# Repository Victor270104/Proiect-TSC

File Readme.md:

# OpenBook

**Autor:** Sandu Victor, 332CC

---

## 1. Descriere generală

Acest proiect propune o platformă hardware pentru dezvoltarea de aplicații IoT și afișare e-paper, cu consum redus de energie. Elementul central este microcontrollerul **ESP32-C6-WROOM-1**, care oferă conectivitate Wi-Fi 6 și Bluetooth Low Energy. Sistemul este proiectat pentru a funcționa atât conectat la USB-C, cât și alimentat de la o baterie Li-Po.

---

## 2. Caracteristici cheie

- **Alimentare prin USB-C**: Simplifică programarea și încărcarea bateriei.
- **Microcontroller ESP32-C6**: Include nucleu RISC-V, Wi-Fi 6, BLE și memorie flash internă de 8MB.
- **Senzori integrați**: BME688 (temperatură, umiditate, presiune, gaze) și DS3231 (ceas de timp real).
- **Stocare suplimentară**:
  - Card SD (SPI)
  - Memorie NOR Flash (W25Q512)
- **Afișaj E-Paper**: Consum ultra-redus, actualizare doar la nevoie.
- **Monitorizare baterie**: MAX17048 pentru nivelul de încărcare.

---

## 3. Structură hardware (sumar)

- **USB-C** și protecții ESD (varistori, diodă TVS).
- **Circuit încărcare Li-Po** cu MCP73831.
- **Regulator LDO** pentru 3.3V stabil.
- **Microcontrollerul ESP32-C6-WROOM-1** (SPI, I2C, GPIO).
- **Senzori**:
  - BME688 (I2C)
  - DS3231 (I2C)
- **Memorii**:
  - Card SD (SPI)
  - W25Q512 (SPI)
- **E-Paper** cu driver SPI și alimentare comutabilă (MOSFET).
- **Butoane** de RESET și BOOT.

*(Diagrama de mai sus este inclusă din `Images/Diagrama.png`.)*

---

## 4. Bill of Materials (BOM)

| Component  | Supplier Link | Datasheet |
|------------|---------------|-----------|
| 112A-TAAR-R03 | [Model](https://store.comet.srl.ro/Catalogue/Product/43497/) | [Datasheet](https://www.snapeda.com/parts/112A-TAAR-R03/Attend/datasheet/) |
| 744043680 | [Model](https://ro.mouser.com/ProductDetail/Wurth-Elektronik/744043680?qs=PGXP4M47uW6VkZq%252BkzjrHA%3D%3D) | [Datasheet](https://www.we-online.com/components/products/datasheet/744043680.pdf) |
| BD5229G-TR | [Model](https://componentsearchengine.com/part-view/BD5229G-TR/ROHM%20Semiconductor) | [Datasheet](https://fscdn.rohm.com/en/products/databook/datasheet/ic/power/voltage_detector/bd52xxg-e.pdf) |
| Capacitor 0402 | [Model](https://ro.mouser.com/c/passive-components/capacitors/ceramic-capacitors/?q=CC0402&srsltid=AfmBOoogjqwwed3xvp6V5-bfVkRuawirfMcnAC47L-UQdC3mnXJk097M) | [Datasheet](https://componentsearchengine.com/Datasheets/2/CC0402MRX5R5BB106.pdf) |
| CPH3225A | [Model](https://www.snapeda.com/parts/CPH3225A/Seiko+Instruments/view-part/?ref=snap) | [Datasheet](https://www.snapeda.com/parts/CPH3225A/Seiko%20Instruments/datasheet/) |
| Custom Button | [Model](https://industry.panasonic.com/global/en/products/control/switch/light-touch/number/evqpuj02k) | [Datasheet](https://industry.panasonic.com/global/en/downloads?tab=catalog&small_g_cd=203&part_no=EVQPUJ02K) |
| DS3231SN | [Model](https://www.snapeda.com/parts/DS3231SN%23/Analog+Devices/view-part/?ref=eda) | [Datasheet](https://www.snapeda.com/parts/DS3231SN%23/Analog%20Devices/datasheet/) |
| ESP32 WROVER 0805 Capacitor | [Model]() | [Datasheet]() |
| ESP32 WROVER BME680 Sensor | [Model](https://www.snapeda.com/parts/BME680/Bosch/view-part/?welcome=home) | [Datasheet](https://www.bosch-sensortec.com/media/boschsensortec/downloads/datasheets/bst-bme680-ds001.pdf) |
| ESP32 WROVER MCP73831 Power Management | [Model](https://www.snapeda.com/parts/BME680/Bosch/view-part/?welcome=home) | [Datasheet](https://www.snapeda.com/parts/MCP73831T-2ACI/OT/Microchip/datasheet/) |
| ESP32C6 Varistor 1812 | [Model]() | [Datasheet]() |
| ESP32C6 WROOM-1-N8| [Model](https://www.snapeda.com/parts/ESP32-C6-WROOM-1-N8/Espressif+Systems/view-part/?ref=eda) | [Datasheet](https://www.snapeda.com/parts/ESP32-C6-WROOM-1-N8/Espressif%20Systems/datasheet/) |
| FH34SRJ-24S-0.5SH | [Model](https://ro.mouser.com/ProductDetail/Hirose-Connector/FH34SRJ-24S-0.5SH99?qs=vcbW%252B4%252BSTIpKBl5ap9J8Fw%3D%3D) | [Datasheet](https://www.snapeda.com/parts/FH34SRJ-24S-0.5SH(99)/Hirose%20Connector/datasheet/) |
| LED Chip 0603 | [Model](https://www.snapeda.com/parts/KP-1608SURCK/Kingbright/view-part/?ref=search&t=LED%200603) | [Datasheet](https://www.snapeda.com/parts/KP-1608SURCK/Kingbright/datasheet/) |
| MAX17048G+T10 | [Model](https://www.snapeda.com/parts/MAX17048G+T10/Analog+Devices/view-part/?ref=eda) | [Datasheet](https://www.snapeda.com/parts/MAX17048G+T10/Analog%20Devices/datasheet/) |
| MBR0530 Schottky Diode | [Model](https://www.snapeda.com/parts/MBR0530/Onsemi/view-part/?ref=snap) | [Datasheet](https://www.snapeda.com/parts/MBR0530/ON%20Semiconductor/datasheet/) |
| PGB1010603MR | [Model](https://www.snapeda.com/parts/PGB1010603MR/Littelfuse/view-part/?ref=eda) | [Datasheet](https://www.snapeda.com/parts/PGB1010603MR/Littelfuse%20Inc./datasheet/) |
| QWIIC Connector | [Model](https://www.snapeda.com/parts/PRT-14417/SparkFun/view-part/) | [Datasheet](https://www.snapeda.com/parts/PRT-14417/SparkFun%20Electronics/datasheet/) |
| RCL CPOL 3528 | [Model](https://www.snapeda.com/parts/CPH3225A/Seiko+Instruments/view-part/?ref=eda) | [Datasheet](https://s3.amazonaws.com/snapeda/datasheet/TAJB475K025RNJ_AVX.pdf) |
| Resistor 0402 | [Model](https://grabcad.com/library/resistor-0402-1) | [Datasheet](https://www.yageo.com/upload/media/product/products/datasheet/rchip/PYu-RC_Group_51_RoHS_L_12.pdf) |
| SI1308EDL-T1-GE3 MOSFET | [Model](https://www.snapeda.com/parts/SI1308EDL-T1-GE3/Vishay+Siliconix/view-part/?welcome=home&ref=eda) | [Datasheet](https://www.snapeda.com/parts/SI1308EDL-T1-GE3/Vishay%20Siliconix/datasheet/) |
| SJ | [Model](https://grabcad.com/library/solder-jumpers-1) | [Datasheet]() |
| USB4110-GF-A | [Model](https://componentsearchengine.com/part-view/USB4110-GF-A/GCT%20(GLOBAL%20CONNECTOR%20TECHNOLOGY)) | [Datasheet](https://gct.co/files/drawings/usb4110.pdf) |
| USBLC6-2SC6Y | [Model](https://www.snapeda.com/parts/USBLC6-2SC6Y/STMicroelectronics/view-part/?welcome=home&ref=eda) | [Datasheet](https://www.snapeda.com/parts/USBLC6-2SC6Y/STMicroelectronics/datasheet/) |
| W25Q512JVEIQ | [Model](https://www.snapeda.com/parts/W25Q512JVEIQ/Winbond+Electronics/view-part/?ref=eda) | [Datasheet](https://www.winbond.com/resource-files/W25Q512JV%20SPI%20RevB%2006252019%20KMS.pdf) |
| XC6220A331MR-G | [Model](https://componentsearchengine.com/part-view/XC6220A331MR-G/Torex) | [Datasheet](https://product.torexsemi.com/system/files/series/xc6220.pdf) |

## 5. Mapare pini ESP32-C6

| Component                | ESP32-C6 Pin(s) | Interface | Purpose |
|--------------------------|----------------|-----------|---------|
| **E-Paper Display**      | IO7 (MOSI), IO6 (SCK), IO10 (CS), IO5 (DC), IO23 (RST), IO3 (BUSY) | SPI | Transfers image data to the display and controls its state. |
| **MicroSD Card**         | IO7 (MOSI), IO6 (SCK), IO4 (SS_SD), IO2 (MISO) | SPI | Allows storage and retrieval of e-book files. |
| **Environmental Sensor (BME688)** | IO21 (SDA), IO22 (SCL) | I2C | Reads temperature, humidity, pressure, and air quality data. |
| **RTC Module (DS3231)**  | IO21 (SDA), IO22 (SCL), IO18 (RST), IO1 (32KHz), IO0 (INT_RTC) | I2C | Keeps track of time even when ESP32 is off. |
| **External NOR Flash**   | IO11 (CS), IO6 (SCK), IO2 (MISO), IO7 (MOSI) | SPI | Provides additional storage for application data. |
| **Battery Monitoring**   | IO21 (SDA), IO22 (SCL) | I2C | Reads battery voltage and charge status. |
| **USB-C Connection**     | GPIOs through voltage regulation | USB | Powers and programs the ESP32-C6. |
| **Control Buttons**      | IO9 (BOOT), IO15 (CHANGE), EN (RESET) | GPIO | User input for device interactions. |
|

## 6. Consum de energie (exemplu)

| Component                | Current Draw (mA) | Voltage (V) | Power (mW) |
|--------------------------|------------------|-------------|------------|
| ESP32-C6 (Wi-Fi active)  |200               |3.3          |660
| E-Paper Display (Updating)               | 40               | 3.3         | 132        |
| BME688 Sensor (Measuring)| 3.1              | 3.3         | 10.23      |
| RTC Module (Active)      | 0.15             | 3.3         | 0.495      |
| SD Card (Active)         | 50               | 3.3         | 165        |
| Externar NOR Flash       | 25               | 3.3         | 82.5       |
| Total Estimated Power Consumption               | ~318.5mA         | 3.3         | 1050.72    |

## 7. Descriere functionala hardware 

###  Arhitectura Hardware

Sistemul este bazat pe microcontrollerul **ESP32-C6-WROOM-1**, cu conectivitate Wi-Fi 6 și BLE, gândit pentru funcționare autonomă și consum redus de energie. Dispozitivul este alimentat de la o baterie Li-Po și poate fi programat prin USB-C. Componentele sunt interconectate prin SPI, I2C și GPIO.

---

### Alimentare și management baterie

- **USB-C Connector & ESD Protection**  
  Conector: `USB4110-GF-A`  
  Protecție ESD: `USBLC6-2SC6Y`

- **LDO Voltage Regulator**  
  Asigură 3.3V stabil pentru întreaga placă

- **Li-Po Battery Charger**  
  MCP73831 – circuit dedicat pentru încărcarea bateriei

- **Battery Gauge (MAX17048)**  
  Măsoară nivelul bateriei și comunică prin I2C

---

### Microcontroller principal

- **ESP32-C6-WROOM-1-N8**  
  RISC-V MCU cu Wi-Fi 6, BLE, 8MB flash intern  
  Rol: control central, comunicare cu senzori, logare, afișare

---

### Stocare

- **SD Card** – pentru loguri de date, firmware, fișiere
- **W25Q512 NOR Flash** – pentru memorie suplimentară SPI (64Mbit)

---

### Senzori & Ceas

- **BME688** – măsoară temperatură, umiditate, presiune și gaze (I2C)
- **DS3231** – ceas de timp real, cu precizie ridicată (I2C)

---

### Afișaj

- **E-Paper Driver + Conector**  
  Conectat prin SPI, controlat de ESP32  
  Alimentarea este comutabilă cu un MOSFET (SI1308EDL)

---

### Control și testare

- **Reset / Boot Buttons**
- **Qwiic/Stemma QT Connector** – extensii I2C
- **Test Pads** – debugging ușor

---

### Protecții

- **TVS Diodes**: `PGB1010603MR` – protecție ESD pe linii sensibile
- **Varistori**: protecție la supratensiuni

---

## 9. Note Adiționale de Proiectare

### Ajustări ale Footprint-urilor

- **Diode (SMD-Hole)**: Footprint-ul inițial avea orificiile pad-urilor prea mici, ceea ce ar fi putut cauza probleme la lipire. Dimensiunea pad-urilor a fost actualizată la **35mil x 190mil** pentru a asigura o producibilitate bună și o conexiune electrică fiabilă.

- **U4 – MAX17048G+T10**: Calea de alimentare VBAT a fost proiectată cu o lățime de **0,3 mm**, pe baza constrângerilor de implementare. Totuși, în footprint, pinii aveau numai **0,27 mm**, cauzând asimetrie și rutare inconsistentă. Dimensiunile pinilor au fost ajustate pentru a se potrivi cu lățimea traseului și a menține simetria designului.

---

### Rutare & Plan de Masă

- **Traseele de alimentare** au fost rutate exclusiv pe stratul superior (Top Layer), necesitând aproximativ **150 de via-uri** pentru a permite rutarea semnalelor pe stratul inferior (Bottom Layer).
- **Planul de masă (GND)** a fost adăugat după ce rutarea a fost finalizată, aplicându-se atât pe stratul superior, cât și pe cel inferior, pentru a obține o împământare cu impedanță redusă și pentru a diminua interferențele EMI.

---

### Poziționarea Componentelor

- **Porturile externe** au fost aliniate cu atenție în raport cu carcasa personalizată OpenBook, pentru a asigura o potrivire corectă și acces ușor.
- **Pad-urile de test (TP)** au fost plasate în apropierea marginilor plăcii și în zone accesibile, pentru a facilita depanarea și testarea.
- **Condenzatoarele de decuplare 100nF** au fost poziționate cât mai aproape de pinii de alimentare ai circuitelor integrate, în conformitate cu practicile standard de reducere a zgomotului.

---

### Probleme de Schematice & Modele 3D

- **Net „GND1”**: A apărut în schematică un net denumit „GND1”, însă acesta nu era vizibil și nu era funcțional conectat la masă. Se presupune că a fost un artefact apărut în timpul procesului de proiectare.
- **Ordinea pinilor la componente 3D**: După finalizarea rutării, actualizarea modelelor 3D a inversat ordinea pinilor la anumite componente cu 2 pini, rupând conexiunile existente. S-a rezolvat prin rotirea acelor modele cu **180°** și realinierea pinilor.

---

### Carcasă & Integrare 3D

- A fost creată o versiune alternativă a carcasei OpenBook, care include o **culoare personalizată** pentru un aspect unic.
- Componentele 3D au fost importate în două moduri diferite, în funcție de frecvența cu care apăreau în schematică.

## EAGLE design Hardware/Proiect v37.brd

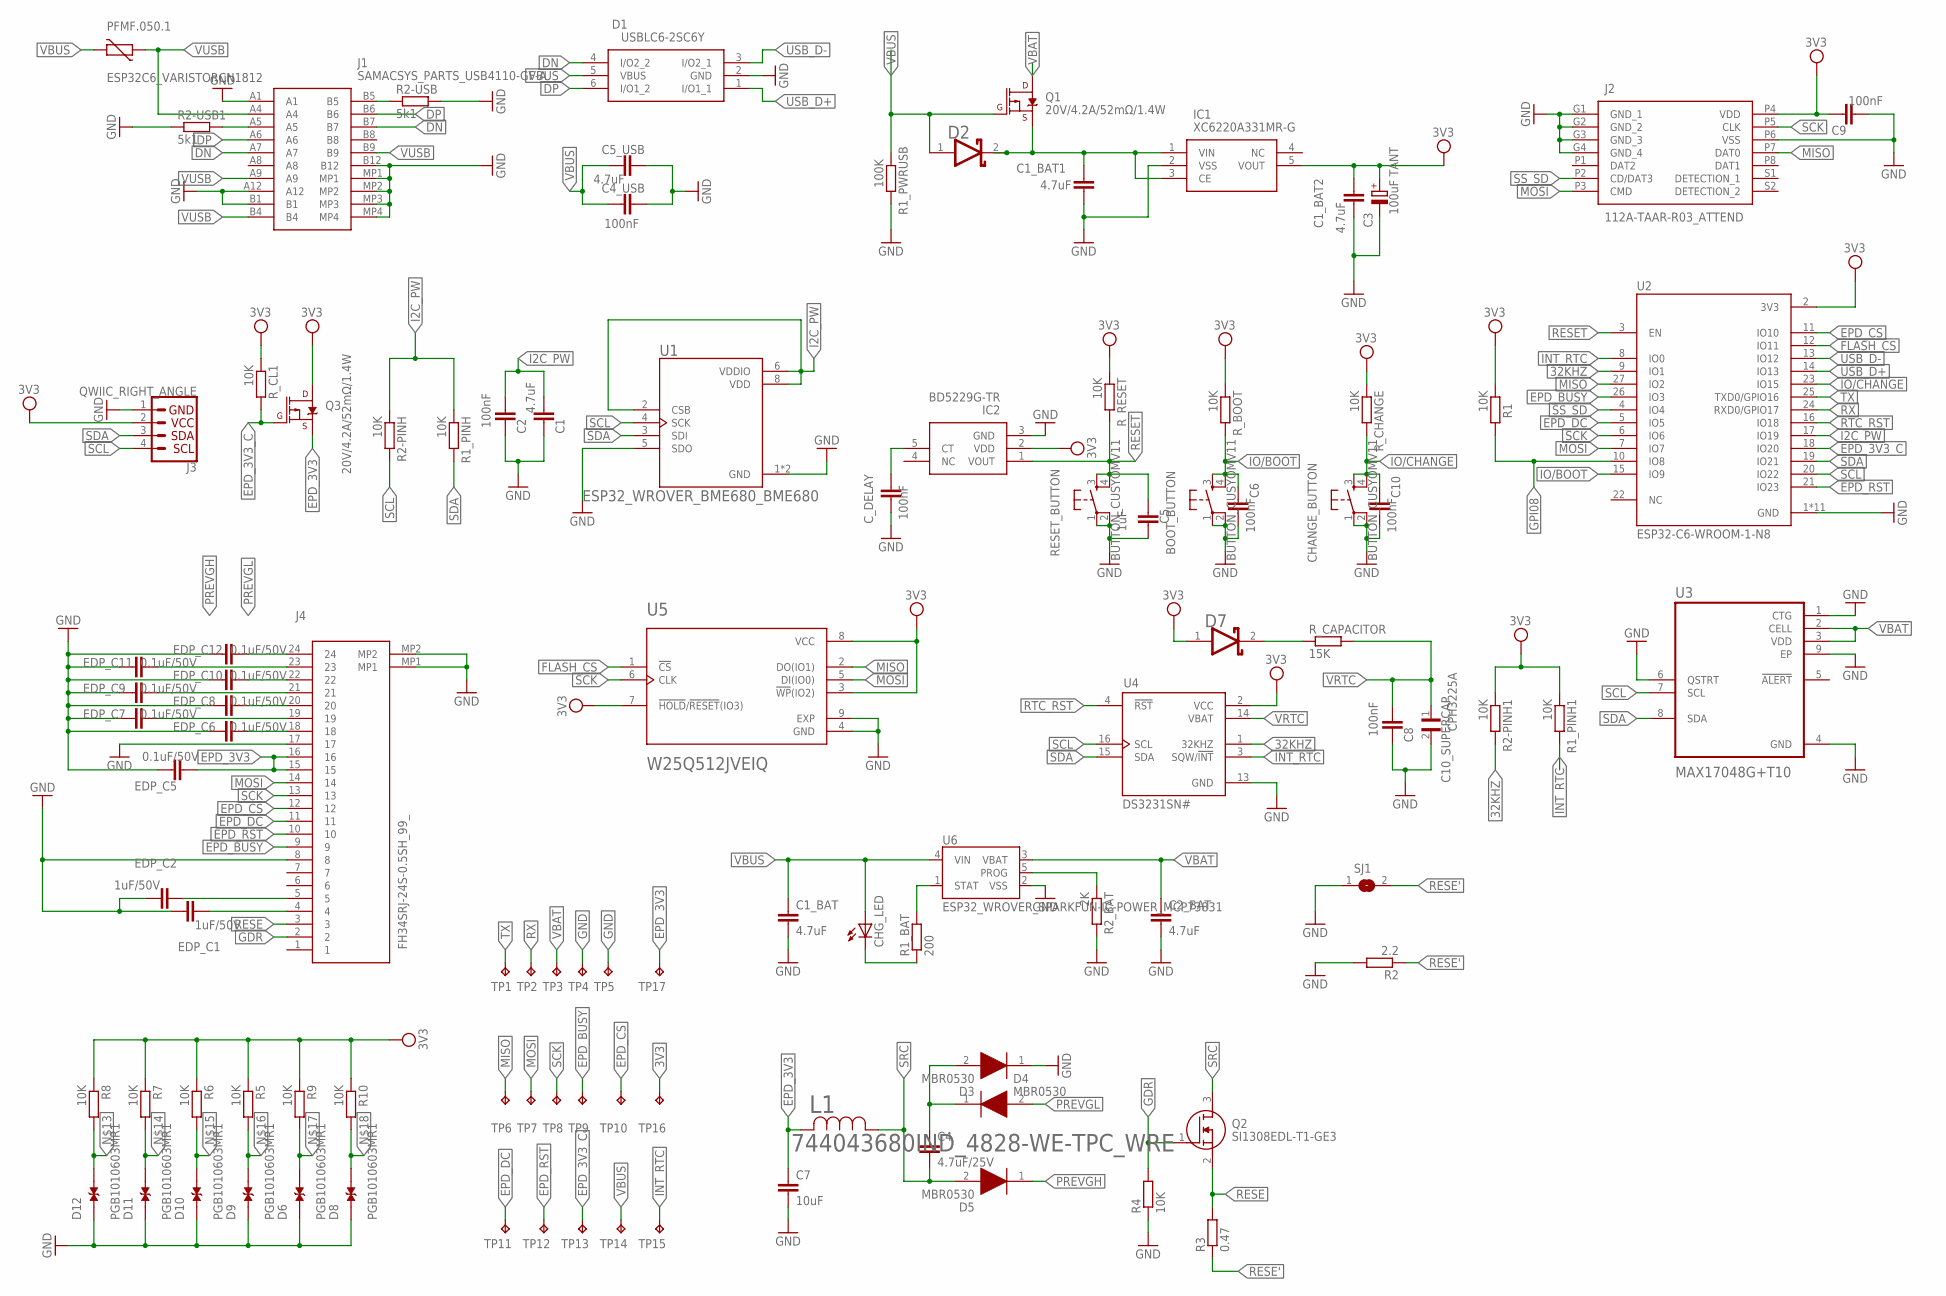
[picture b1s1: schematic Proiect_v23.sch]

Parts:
BOOT_BUTTON: BUTTON_CUSYOMV11; MYBUTTON
C1, C1_BAT, C1_BAT1, C1_BAT2, C2_BAT, C5_USB: 4.7uF; ESP32_WROVER_EAGLE-LTSPICE_C0402
C2, C4_USB, C6, C8, C9, C10: 100nF; ESP32_WROVER_EAGLE-LTSPICE_C0402
C3: 100uF TANT; RCL_CT3528
C4: 4.7uF/25V; ESP32_WROVER_EAGLE-LTSPICE_C0402
C5: 1uF; ESP32_WROVER_EAGLE-LTSPICE_C0402
C7: 10uF; ESP32_WROVER_EAGLE-LTSPICE_C0402
C10_SUPERCAP: CPH3225A; CAPCP3225X100N
CHANGE_BUTTON: BUTTON_CUSYOMV11; MYBUTTON
CHG_LED: ADAFRUIT_LEDCHIP-LED0603; ADAFRUIT_CHIP-LED0603
C_DELAY: 100nF; ESP32_WROVER_EAGLE-LTSPICE_C0402
D1: USBLC6-2SC6Y; SOT95P280X145-6N
D2, D7: ESP32_WROVER_AVX---SD0805S020S1R0_AVX_SD0805S020S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; ESP32_WROVER_AVX---SD0805S020S1R0_AVX_SD0805S020S1R0_0
D3, D4, D5: MBR0530; SOD3716X135N
D6, D8, D9, D10, D11, D12: PGB1010603MR1; DIOC1608X36N
EDP_C1, EDP_C2: 1uF/50V; ESP32_WROVER_EAGLE-LTSPICE_C0402
EDP_C5, EDP_C6, EDP_C7, EDP_C8, EDP_C9, EDP_C10, EDP_C11, EDP_C12: 0.1uF/50V; ESP32_WROVER_EAGLE-LTSPICE_C0402
IC1: XC6220A331MR-G; SOT95P280X120-5N
IC2: BD5229G-TR; SOT95P280X125-5N
J1: SAMACSYS_PARTS_USB4110-GF-A; SAMACSYS_PARTS_USB4110GFA
J2: 112A-TAAR-R03_ATTEND; 112ATAARR03ATTEND
J3: QWIIC_RIGHT_ANGLE; JST04_1MM_RA
J4: FH34SRJ-24S-0.5SH_99_; FH34SRJ24S05SH99
L1: 744043680IND_4828-WE-TPC_WRE; IND_4828-WE-TPC_WRE
PFMF.050.1: ESP32C6_VARISTORCN1812; ESP32C6_VARISTOR_CT/CN1812
Q1, Q3: 20V/4.2A/52mΩ/1.4W; ESP32_WROVER_SPARKFUN-DISCRETESEMI_SOT23-3
Q2: SI1308EDL-T1-GE3; SOT65P210X110-3N
R1, R1_PINH, R1_PINH1, R2-PINH, R2-PINH1, R4, R5, R6, R7, R8, R9, R10: 10K; ESP32_WROVER_EAGLE-LTSPICE_R0402
R1_BAT: 200; ESP32_WROVER_EAGLE-LTSPICE_R0402
R1_PWRUSB: 100K; ESP32_WROVER_EAGLE-LTSPICE_R0402
R2: 2.2; ESP32_WROVER_EAGLE-LTSPICE_R0402
R2-USB, R2-USB1: 5k1; ESP32_WROVER_EAGLE-LTSPICE_R0402
R2_BAT: 2K; ESP32_WROVER_EAGLE-LTSPICE_R0402
R3: 0.47; ESP32_WROVER_EAGLE-LTSPICE_R0402
RESET_BUTTON: BUTTON_CUSYOMV11; MYBUTTON
R_BOOT: 10K; ESP32_WROVER_EAGLE-LTSPICE_R0402
R_CAPACITOR: 15K; ESP32_WROVER_EAGLE-LTSPICE_R0402
R_CHANGE: 10K; ESP32_WROVER_EAGLE-LTSPICE_R0402
R_CL1: 10K; ESP32_WROVER_EAGLE-LTSPICE_R0402
R_RESET: 10K; ESP32_WROVER_EAGLE-LTSPICE_R0402
SJ1: SJ
TP1, TP2, TP3, TP4, TP5, TP6, TP7, TP8, TP9, TP10, TP11, TP12, TP13, TP14, TP15, TP16, TP17: TP; TP20R
U1: ESP32_WROVER_BME680_BME680; ESP32_WROVER_BME680_PSON80P300X300X100-8N
U2: ESP32-C6-WROOM-1-N8; XCVR_ESP32-C6-WROOM-1-N8
U3: MAX17048G+T10; SON50P200X200X80-9N
U4: DS3231SN#; SOIC127P1032X265-16N
U5: W25Q512JVEIQ; SON127P600X800X80-9N
U6: ESP32_WROVER_SPARKFUN-IC-POWER_MCP73831; ESP32_WROVER_SPARKFUN-IC-POWER_SOT23-5

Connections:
3V3: C1_BAT2.1, C3.+, C9.2, D7.1 (ANODE), IC1.5 (VOUT), IC2.2 (VDD), J2.P4 (VDD), J3.2, Q3.3 (D), R1.1, R1_PINH1.1, R2-PINH1.1, R5.1, R6.1, R7.1, R8.1, R9.1, R10.1, R_BOOT.1, R_CHANGE.1, R_CL1.1, R_RESET.1, TP16.TP, U2.2 (3V3), U4.2 (VCC), U5.3 (!WP!(IO2)), U5.7 (!HOLD!/!RESET!(IO3)), U5.8 (VCC)
32KHZ: R2-PINH1.2, U2.9 (IO1), U4.1 (32KHZ)
DN: D1.4 (I/O2_2), J1.A7, J1.B7
DP: D1.6 (I/O1_2), J1.A6, J1.B6
EPD_3V3: C7.1, EDP_C5.1, J4.15, J4.16, L1.2, Q3.2 (S), TP17.TP
EPD_3V3_C: Q3.1 (G), R_CL1.2, TP13.TP, U2.18 (IO20)
EPD_BUSY: J4.9, TP9.TP, U2.26 (IO3)
EPD_CS: J4.12, TP10.TP, U2.11 (IO10)
EPD_DC: J4.11, TP11.TP, U2.5 (IO5)
EPD_RST: J4.10, TP12.TP, U2.21 (IO23)
FLASH_CS: U2.12 (IO11), U5.1 (!CS)
GDR: J4.2, Q2.1 (G), R4.2
GND: BOOT_BUTTON.1, BOOT_BUTTON.2, C1.2, C1_BAT.2, C1_BAT1.2, C1_BAT2.2, C2.2, C2_BAT.2, C3.-, C4_USB.2, C5.2, C5_USB.2, C6.2, C7.2, C8.2, C9.1, C10.2, C10_SUPERCAP.2, CHANGE_BUTTON.1, CHANGE_BUTTON.2, C_DELAY.2, D1.2 (GND), D3.1 (K), D6.1, D8.1, D9.1, D10.1, D11.1, D12.1, EDP_C1.1, EDP_C2.2, EDP_C5.2, EDP_C6.2, EDP_C7.2, EDP_C8.2, EDP_C9.2, EDP_C10.2, EDP_C11.2, EDP_C12.2, IC1.2 (VSS), IC2.3 (GND), J1.A1, J1.A12, J1.B1, J1.B12, J1.MP1, J1.MP2, J1.MP3, J1.MP4, J2.G1 (GND_1), J2.G2 (GND_2), J2.G3 (GND_3), J2.G4 (GND_4), J2.P6 (VSS), J3.1, J4.8, J4.17, J4.MP1, J4.MP2, R1_PWRUSB.2, R2.2, R2-USB.2, R2-USB1.1, R2_BAT.2, R4.1, RESET_BUTTON.1, RESET_BUTTON.2, SJ1.1, TP4.TP, TP5.TP, U1.1 (GND), U1.5 (SDO), U1.7 (GND), U2.1 (GND), U2.28 (GND), U2.29_1 (GND), U2.29_2 (GND), U2.29_3 (GND), U2.29_4 (GND), U2.29_5 (GND), U2.29_6 (GND), U2.29_7 (GND), U2.29_8 (GND), U2.29_9 (GND), U3.1 (CTG), U3.4 (GND), U3.6 (QSTRT), U3.9 (EP), U4.13 (GND), U5.4 (GND), U5.9 (EXP), U6.2 (VSS)
GPI08: R1.2, U2.10 (IO8)
I2C_PW: C1.1, C2.1, R1_PINH.1, R2-PINH.1, U1.2 (CSB), U1.6 (VDDIO), U1.8 (VDD), U2.17 (IO19)
INT_RTC: R1_PINH1.2, TP15.TP, U2.8 (IO0), U4.3 (SQW/!INT)
IO/BOOT: BOOT_BUTTON.3, BOOT_BUTTON.4, C6.1, R_BOOT.2, U2.15 (IO9)
IO/CHANGE: C10.1, CHANGE_BUTTON.3, CHANGE_BUTTON.4, R_CHANGE.2, U2.23 (IO15)
MISO: J2.P7 (DAT0), TP6.TP, U2.27 (IO2), U5.2 (DO(IO1))
MOSI: J2.P3 (CMD), J4.14, TP7.TP, U2.7 (IO7), U5.5 (DI(IO0))
unnamed: EDP_C6.1, J4.18
unnamed: C1_BAT1.1, D2.2 (CATHODE), IC1.1 (VIN), IC1.3 (CE), Q1.2 (S)
unnamed: J1.A5, R2-USB1.2
unnamed: EDP_C7.1, J4.19
unnamed: EDP_C1.2, J4.4
unnamed: EDP_C2.1, J4.5
unnamed: EDP_C8.1, J4.20
unnamed: C_DELAY.1, IC2.5 (CT)
unnamed: EDP_C12.1, J4.24
unnamed: D7.2 (CATHODE), R_CAPACITOR.1
unnamed: J1.B5, R2-USB.1
unnamed: EDP_C10.1, J4.22
unnamed: D12.2, R8.2
unnamed: D11.2, R7.2
unnamed: D10.2, R6.2
unnamed: D9.2, R5.2
unnamed: D6.2, R9.2
unnamed: D8.2, R10.2
unnamed: R1_BAT.2, U6.1 (STAT)
unnamed: CHG_LED.C, R1_BAT.1
unnamed: R2_BAT.1, U6.5 (PROG)
unnamed: C4.1, D3.2 (A), D4.1 (K)
PREVGH: D5.1 (K), EDP_C9.1, J4.21
PREVGL: D4.2 (A), EDP_C11.1, J4.23
RESE: J4.3, Q2.2 (S), R3.2
RESE': R2.1, R3.1, SJ1.2
RESET: C5.1, IC2.1 (VOUT), RESET_BUTTON.3, RESET_BUTTON.4, R_RESET.2, U2.3 (EN)
RTC_RST: U2.16 (IO18), U4.4 (!RST)
RX: TP2.TP, U2.24 (RXD0/GPIO17)
SCK: J2.P5 (CLK), J4.13, TP8.TP, U2.6 (IO6), U5.6 (CLK)
SCL: J3.4, R2-PINH.2, U1.4 (SCK), U2.20 (IO22), U3.7 (SCL), U4.16 (SCL)
SDA: J3.3, R1_PINH.2, U1.3 (SDI), U2.19 (IO21), U3.8 (SDA), U4.15 (SDA)
SRC: C4.2, D5.2 (A), L1.1, Q2.3 (D)
SS_SD: J2.P2 (CD/DAT3), U2.4 (IO4)
TX: TP1.TP, U2.25 (TXD0/GPIO16)
USB_D+: D1.1 (I/O1_1), U2.14 (IO13)
USB_D-: D1.3 (I/O2_1), U2.13 (IO12)
VBAT: C2_BAT.1, Q1.3 (D), TP3.TP, U3.2 (CELL), U3.3 (VDD), U6.3 (VBAT)
VBUS: C1_BAT.1, C4_USB.1, C5_USB.1, CHG_LED.A, D1.5 (VBUS), D2.1 (ANODE), PFMF.050.1.2, Q1.1 (G), R1_PWRUSB.1, TP14.TP, U6.4 (VIN)
VRTC: C8.1, C10_SUPERCAP.1, R_CAPACITOR.2, U4.14 (VBAT)
VUSB: J1.A4, J1.A9, J1.B4, J1.B9, PFMF.050.1.1

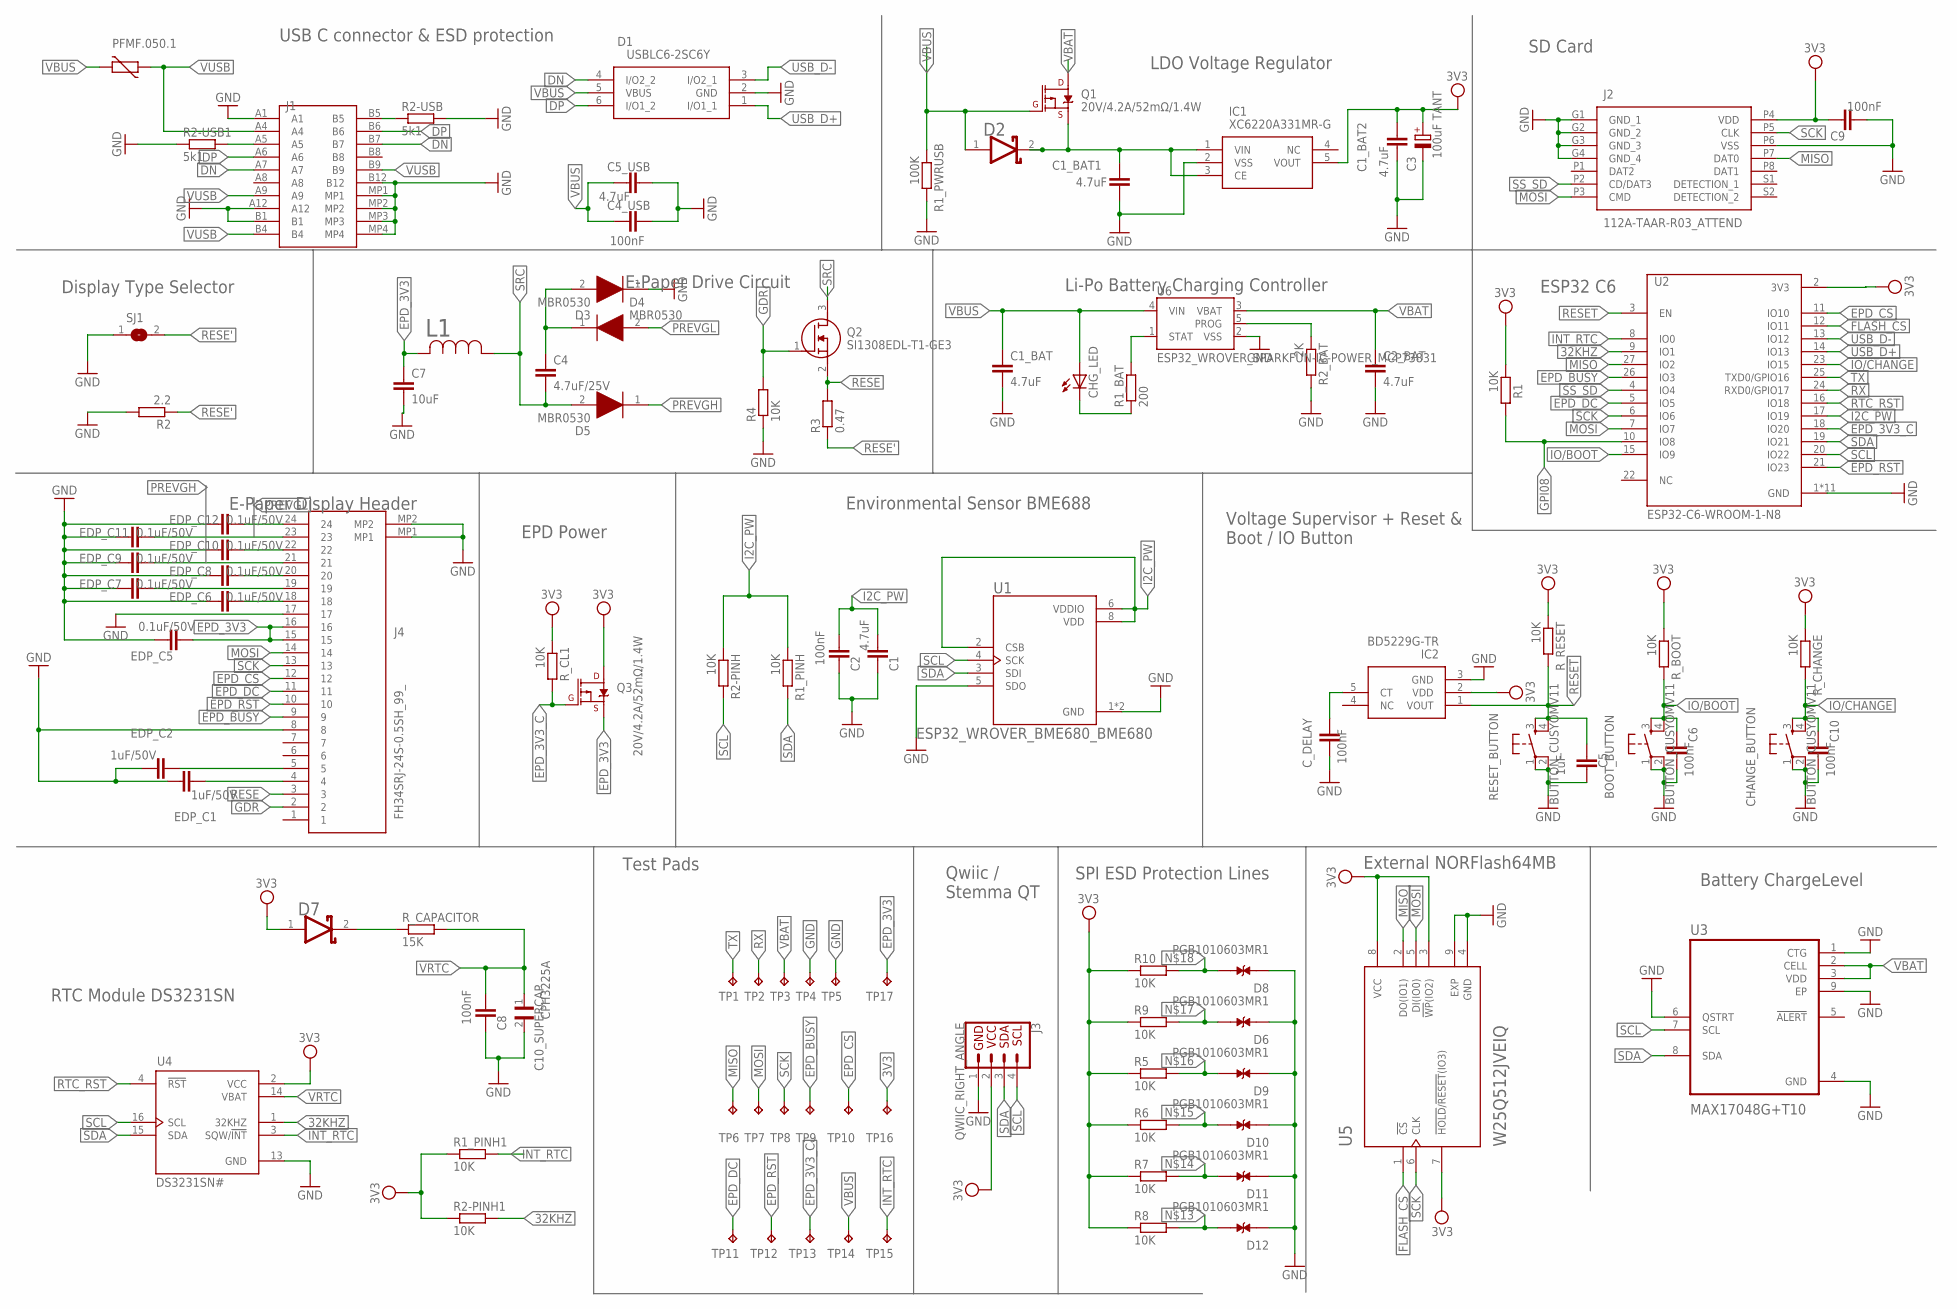
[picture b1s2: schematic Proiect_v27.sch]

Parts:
BOOT_BUTTON: BUTTON_CUSYOMV11; MYBUTTON
C1, C1_BAT, C1_BAT1, C1_BAT2, C2_BAT, C5_USB: 4.7uF; ESP32_WROVER_EAGLE-LTSPICE_C0402
C2, C4_USB, C6, C8, C9, C10: 100nF; ESP32_WROVER_EAGLE-LTSPICE_C0402
C3: 100uF TANT; RCL_CT3528
C4: 4.7uF/25V; ESP32_WROVER_EAGLE-LTSPICE_C0402
C5: 1uF; ESP32_WROVER_EAGLE-LTSPICE_C0402
C7: 10uF; ESP32_WROVER_EAGLE-LTSPICE_C0402
C10_SUPERCAP: CPH3225A; CAPCP3225X100N
CHANGE_BUTTON: BUTTON_CUSYOMV11; MYBUTTON
CHG_LED: ADAFRUIT_LEDCHIP-LED0603; ADAFRUIT_CHIP-LED0603
C_DELAY: 100nF; ESP32_WROVER_EAGLE-LTSPICE_C0402
D1: USBLC6-2SC6Y; SOT95P280X145-6N
D2, D7: ESP32_WROVER_AVX---SD0805S020S1R0_AVX_SD0805S020S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; ESP32_WROVER_AVX---SD0805S020S1R0_AVX_SD0805S020S1R0_0
D3, D4, D5: MBR0530; SOD3716X135N
D6, D8, D9, D10, D11, D12: PGB1010603MR1; DIOC1608X36N
EDP_C1, EDP_C2: 1uF/50V; ESP32_WROVER_EAGLE-LTSPICE_C0402
EDP_C5, EDP_C6, EDP_C7, EDP_C8, EDP_C9, EDP_C10, EDP_C11, EDP_C12: 0.1uF/50V; ESP32_WROVER_EAGLE-LTSPICE_C0402
IC1: XC6220A331MR-G; SOT95P280X120-5N
IC2: BD5229G-TR; SOT95P280X125-5N
J1: SAMACSYS_PARTS_USB4110-GF-A; SAMACSYS_PARTS_USB4110GFA
J2: 112A-TAAR-R03_ATTEND; 112ATAARR03ATTEND
J3: QWIIC_RIGHT_ANGLE; JST04_1MM_RA
J4: FH34SRJ-24S-0.5SH_99_; FH34SRJ24S05SH99
L1: 744043680IND_4828-WE-TPC_WRE; IND_4828-WE-TPC_WRE
PFMF.050.1: ESP32C6_VARISTORCN1812; ESP32C6_VARISTOR_CT/CN1812
Q1, Q3: 20V/4.2A/52mΩ/1.4W; ESP32_WROVER_SPARKFUN-DISCRETESEMI_SOT23-3
Q2: SI1308EDL-T1-GE3; SOT65P210X110-3N
R1, R1_PINH, R1_PINH1, R2-PINH, R2-PINH1, R4, R5, R6, R7, R8, R9, R10: 10K; ESP32_WROVER_EAGLE-LTSPICE_R0402
R1_BAT: 200; ESP32_WROVER_EAGLE-LTSPICE_R0402
R1_PWRUSB: 100K; ESP32_WROVER_EAGLE-LTSPICE_R0402
R2: 2.2; ESP32_WROVER_EAGLE-LTSPICE_R0402
R2-USB, R2-USB1: 5k1; ESP32_WROVER_EAGLE-LTSPICE_R0402
R2_BAT: 2K; ESP32_WROVER_EAGLE-LTSPICE_R0402
R3: 0.47; ESP32_WROVER_EAGLE-LTSPICE_R0402
RESET_BUTTON: BUTTON_CUSYOMV11; MYBUTTON
R_BOOT: 10K; ESP32_WROVER_EAGLE-LTSPICE_R0402
R_CAPACITOR: 15K; ESP32_WROVER_EAGLE-LTSPICE_R0402
R_CHANGE: 10K; ESP32_WROVER_EAGLE-LTSPICE_R0402
R_CL1: 10K; ESP32_WROVER_EAGLE-LTSPICE_R0402
R_RESET: 10K; ESP32_WROVER_EAGLE-LTSPICE_R0402
SJ1: SJ
TP1, TP2, TP3, TP4, TP5, TP6, TP7, TP8, TP9, TP10, TP11, TP12, TP13, TP14, TP15, TP16, TP17: TP; TP20R
U1: ESP32_WROVER_BME680_BME680; ESP32_WROVER_BME680_PSON80P300X300X100-8N
U2: ESP32-C6-WROOM-1-N8; XCVR_ESP32-C6-WROOM-1-N8
U3: MAX17048G+T10; SON50P200X200X80-9N
U4: DS3231SN#; SOIC127P1032X265-16N
U5: W25Q512JVEIQ; SON127P600X800X80-9N
U6: ESP32_WROVER_SPARKFUN-IC-POWER_MCP73831; ESP32_WROVER_SPARKFUN-IC-POWER_SOT23-5

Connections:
3V3: C1_BAT2.1, C3.+, C9.2, D7.1 (ANODE), IC1.5 (VOUT), IC2.2 (VDD), J2.P4 (VDD), J3.2, Q3.3 (D), R1.1, R1_PINH1.1, R2-PINH1.1, R5.1, R6.1, R7.1, R8.1, R9.1, R10.1, R_BOOT.1, R_CHANGE.1, R_CL1.1, R_RESET.1, TP16.TP, U2.2 (3V3), U4.2 (VCC), U5.3 (!WP!(IO2)), U5.7 (!HOLD!/!RESET!(IO3)), U5.8 (VCC)
32KHZ: R2-PINH1.2, U2.9 (IO1), U4.1 (32KHZ)
DN: D1.4 (I/O2_2), J1.A7, J1.B7
DP: D1.6 (I/O1_2), J1.A6, J1.B6
EPD_3V3: C7.1, EDP_C5.1, J4.15, J4.16, L1.2, Q3.2 (S), TP17.TP
EPD_3V3_C: Q3.1 (G), R_CL1.2, TP13.TP, U2.18 (IO20)
EPD_BUSY: J4.9, TP9.TP, U2.26 (IO3)
EPD_CS: J4.12, TP10.TP, U2.11 (IO10)
EPD_DC: J4.11, TP11.TP, U2.5 (IO5)
EPD_RST: J4.10, TP12.TP, U2.21 (IO23)
FLASH_CS: U2.12 (IO11), U5.1 (!CS)
GDR: J4.2, Q2.1 (G), R4.2
GND: BOOT_BUTTON.1, BOOT_BUTTON.2, C1.2, C1_BAT.2, C1_BAT1.2, C1_BAT2.2, C2.2, C2_BAT.2, C3.-, C4_USB.2, C5.2, C5_USB.2, C6.2, C7.2, C8.2, C9.1, C10.2, C10_SUPERCAP.2, CHANGE_BUTTON.1, CHANGE_BUTTON.2, C_DELAY.2, D1.2 (GND), D3.1 (K), D6.1, D8.1, D9.1, D10.1, D11.1, D12.1, EDP_C1.1, EDP_C2.2, EDP_C5.2, EDP_C6.2, EDP_C7.2, EDP_C8.2, EDP_C9.2, EDP_C10.2, EDP_C11.2, EDP_C12.2, IC1.2 (VSS), IC2.3 (GND), J1.A1, J1.A12, J1.B1, J1.B12, J1.MP1, J1.MP2, J1.MP3, J1.MP4, J2.G1 (GND_1), J2.G2 (GND_2), J2.G3 (GND_3), J2.G4 (GND_4), J2.P6 (VSS), J3.1, J4.8, J4.17, J4.MP1, J4.MP2, R1_PWRUSB.2, R2.2, R2-USB.2, R2-USB1.1, R2_BAT.2, R4.1, RESET_BUTTON.1, RESET_BUTTON.2, SJ1.1, TP4.TP, TP5.TP, U1.1 (GND), U1.5 (SDO), U1.7 (GND), U2.1 (GND), U2.28 (GND), U2.29_1 (GND), U2.29_2 (GND), U2.29_3 (GND), U2.29_4 (GND), U2.29_5 (GND), U2.29_6 (GND), U2.29_7 (GND), U2.29_8 (GND), U2.29_9 (GND), U3.1 (CTG), U3.4 (GND), U3.6 (QSTRT), U3.9 (EP), U4.13 (GND), U5.4 (GND), U5.9 (EXP), U6.2 (VSS)
GPI08: R1.2, U2.10 (IO8)
I2C_PW: C1.1, C2.1, R1_PINH.1, R2-PINH.1, U1.2 (CSB), U1.6 (VDDIO), U1.8 (VDD), U2.17 (IO19)
INT_RTC: R1_PINH1.2, TP15.TP, U2.8 (IO0), U4.3 (SQW/!INT)
IO/BOOT: BOOT_BUTTON.3, BOOT_BUTTON.4, C6.1, R_BOOT.2, U2.15 (IO9)
IO/CHANGE: C10.1, CHANGE_BUTTON.3, CHANGE_BUTTON.4, R_CHANGE.2, U2.23 (IO15)
MISO: J2.P7 (DAT0), TP6.TP, U2.27 (IO2), U5.2 (DO(IO1))
MOSI: J2.P3 (CMD), J4.14, TP7.TP, U2.7 (IO7), U5.5 (DI(IO0))
unnamed: EDP_C6.1, J4.18
unnamed: C1_BAT1.1, D2.2 (CATHODE), IC1.1 (VIN), IC1.3 (CE), Q1.2 (S)
unnamed: J1.A5, R2-USB1.2
unnamed: EDP_C7.1, J4.19
unnamed: EDP_C1.2, J4.4
unnamed: EDP_C2.1, J4.5
unnamed: EDP_C8.1, J4.20
unnamed: C_DELAY.1, IC2.5 (CT)
unnamed: EDP_C12.1, J4.24
unnamed: D7.2 (CATHODE), R_CAPACITOR.1
unnamed: J1.B5, R2-USB.1
unnamed: EDP_C10.1, J4.22
unnamed: D12.2, R8.2
unnamed: D11.2, R7.2
unnamed: D10.2, R6.2
unnamed: D9.2, R5.2
unnamed: D6.2, R9.2
unnamed: D8.2, R10.2
unnamed: R1_BAT.2, U6.1 (STAT)
unnamed: CHG_LED.C, R1_BAT.1
unnamed: R2_BAT.1, U6.5 (PROG)
unnamed: C4.1, D3.2 (A), D4.1 (K)
PREVGH: D5.1 (K), EDP_C9.1, J4.21
PREVGL: D4.2 (A), EDP_C11.1, J4.23
RESE: J4.3, Q2.2 (S), R3.2
RESE': R2.1, R3.1, SJ1.2
RESET: C5.1, IC2.1 (VOUT), RESET_BUTTON.3, RESET_BUTTON.4, R_RESET.2, U2.3 (EN)
RTC_RST: U2.16 (IO18), U4.4 (!RST)
RX: TP2.TP, U2.24 (RXD0/GPIO17)
SCK: J2.P5 (CLK), J4.13, TP8.TP, U2.6 (IO6), U5.6 (CLK)
SCL: J3.4, R2-PINH.2, U1.4 (SCK), U2.20 (IO22), U3.7 (SCL), U4.16 (SCL)
SDA: J3.3, R1_PINH.2, U1.3 (SDI), U2.19 (IO21), U3.8 (SDA), U4.15 (SDA)
SRC: C4.2, D5.2 (A), L1.1, Q2.3 (D)
SS_SD: J2.P2 (CD/DAT3), U2.4 (IO4)
TX: TP1.TP, U2.25 (TXD0/GPIO16)
USB_D+: D1.1 (I/O1_1), U2.14 (IO13)
USB_D-: D1.3 (I/O2_1), U2.13 (IO12)
VBAT: C2_BAT.1, Q1.3 (D), TP3.TP, U3.2 (CELL), U3.3 (VDD), U6.3 (VBAT)
VBUS: C1_BAT.1, C4_USB.1, C5_USB.1, CHG_LED.A, D1.5 (VBUS), D2.1 (ANODE), PFMF.050.1.2, Q1.1 (G), R1_PWRUSB.1, TP14.TP, U6.4 (VIN)
VRTC: C8.1, C10_SUPERCAP.1, R_CAPACITOR.2, U4.14 (VBAT)
VUSB: J1.A4, J1.A9, J1.B4, J1.B9, PFMF.050.1.1

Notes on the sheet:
USB C connector & ESD protection
LDO Voltage Regulator
SD Card
ESP32 C6
Li-Po Battery Charging Controller
E-Paper Drive Circuit
Display Type Selector
E-Paper Display Header
EPD Power
Environmental Sensor BME688
Voltage Supervisor + Reset & Boot / IO Button
Battery ChargeLevel
RTC Module DS3231SN
Test Pads
Qwiic / Stemma QT
SPI ESD Protection Lines
External NORFlash64MB

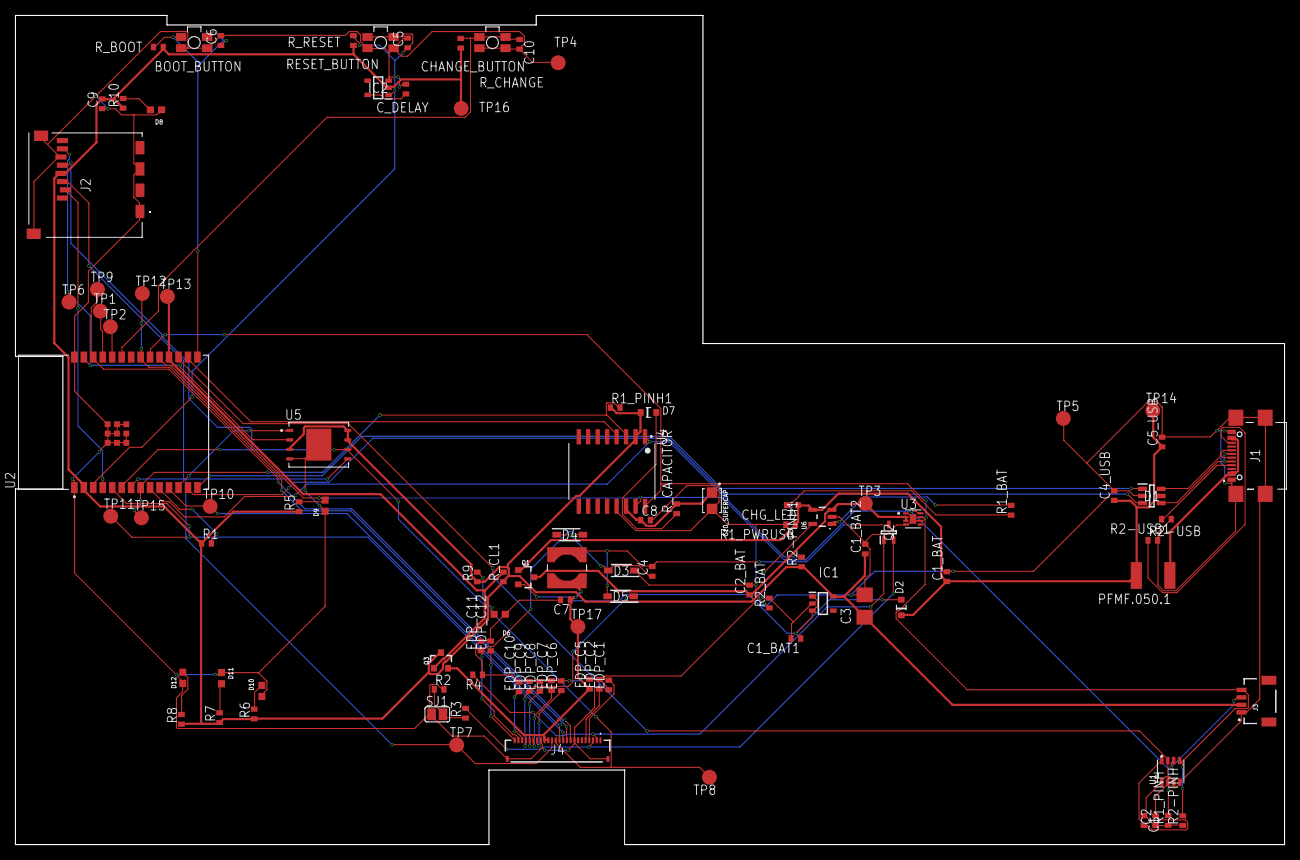
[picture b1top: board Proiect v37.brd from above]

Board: 2 copper layers, 170.2 x 111.2 mm, 103 parts (0 on the bottom side), 61 nets.

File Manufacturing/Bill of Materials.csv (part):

Qty,Value,Device,Package,Parts,Description,ARROW_PART_NUMBER,ARROW_PRICE-STOCK,AVAILABILITY,CHECK_PRICES,COPYRIGHT,DESCRIPTION,HEIGHT,MANUFACTURER_NAME,MANUFACTURER_PART_NUMBER,MF,MFR_NAME,MOUSER_PART_NUMBER,MOUSER_PRICE-STOCK,MOUSER_TESTING_PART_NUMBER,MOUSER_TESTING_PRICE-STOCK,MP,PACKAGE,POPULARITY,PRICE,PROD_ID,PURCHASE-URL,SNAPEDA_LINK,SPICEMODEL,SPICEPREFIX,VALUE
1,,ADAFRUIT_LEDCHIP-LED0603,ADAFRUIT_CHIP-LED0603,CHG_LED,LED,,,,,,,,,,,,,,,,,,,,,,,,,
1,,SJ,SJ,SJ1,"SMD solder JUMPER",,,,,,,,,,,,,,,,,,3,,,,,,,
8,0.1uF/50V,EAGLE-LTSPICE_C,ESP32_WROVER_EAGLE-LTSPICE_C0402,"EDP_C5, EDP_C6, EDP_C7, EDP_C8, EDP_C9, EDP_C10, EDP_C11, EDP_C12","CAPACITOR, European symbol",,,,,,,,,,,,,,,,,,,,,,,,,
1,0.47,ESP32_WROVER_EAGLE-LTSPICE_R,ESP32_WROVER_EAGLE-LTSPICE_R0402,R3,"RESISTOR, European symbol",,,,,,,,,,,,,,,,,,,,,,,,,
1,100K,ESP32_WROVER_EAGLE-LTSPICE_R,ESP32_WROVER_EAGLE-LTSPICE_R0402,R1_PWRUSB,"RESISTOR, European symbol",,,,,,,,,,,,,,,,,,,,,,,,,
7,100nF,EAGLE-LTSPICE_C,ESP32_WROVER_EAGLE-LTSPICE_C0402,"C2, C4_USB, C6, C8, C9, C10, C_DELAY","CAPACITOR, European symbol",,,,,,,,,,,,,,,,,,,,,,,,,
1,"100uF TANT",RCL_CPOL-EUCT3528,RCL_CT3528,C3,"POLARIZED CAPACITOR, European symbol",,,,,,,,,,,,,,,,,,0,,,,,,C,
16,10K,ESP32_WROVER_EAGLE-LTSPICE_R,ESP32_WROVER_EAGLE-LTSPICE_R0402,"R1, R1_PINH, R1_PINH1, R2-PINH, R2-PINH1, R4, R5, R6, R7, R8, R9, R10, R_BOOT, R_CHANGE, R_CL1, R_RESET","RESISTOR, European symbol",,,,,,,,,,,,,,,,,,,,,,,,,
1,10uF,ESP32_WROVER_EAGLE-LTSPICE_CC0402,ESP32_WROVER_EAGLE-LTSPICE_C0402,C7,"CAPACITOR, European symbol",,,,,,,,,,,,,,,,,,,,,,,NONE,C,
1,112A-TAAR-R03_ATTEND,112A-TAAR-R03_ATTEND,112ATAARR03ATTEND,J2,"Micro SD Card Socket, Push-Push Type, Top Mount, SMT, H=1.83mm, 10u",,,,,,"Micro SD Card Socket"," Push-Push Type"," Top Mount"," SMT"," H=1.83mm"," 10u",1.9mm,ATTEND,"112A-TAAR-R03 ATTEND",,,,,,,,,,,
1,15K,ESP32_WROVER_EAGLE-LTSPICE_R,ESP32_WROVER_EAGLE-LTSPICE_R0402,R_CAPACITOR,"RESISTOR, European symbol",,,,,,,,,,,,,,,,,,,,,,,,,
1,1uF,EAGLE-LTSPICE_C,ESP32_WROVER_EAGLE-LTSPICE_C0402,C5,"CAPACITOR, European symbol",,,,,,,,,,,,,,,,,,,,,,,,,
2,1uF/50V,EAGLE-LTSPICE_C,ESP32_WROVER_EAGLE-LTSPICE_C0402,"EDP_C1, EDP_C2","CAPACITOR, European symbol",,,,,,,,,,,,,,,,,,,,,,,,,
1,2.2,ESP32_WROVER_EAGLE-LTSPICE_R,ESP32_WROVER_EAGLE-LTSPICE_R0402,R2,"RESISTOR, European symbol",,,,,,,,,,,,,,,,,,,,,,,,,
1,200,ESP32_WROVER_EAGLE-LTSPICE_R,ESP32_WROVER_EAGLE-LTSPICE_R0402,R1_BAT,"RESISTOR, European symbol",,,,,,,,,,,,,,,,,,,,,,,,,
2,20V/4.2A/52m?/1.4W,ESP32_WROVER_SPARKFUN-DISCRETESEMI_MOSFET_PCH-DMG2305UX-7,ESP32_WROVER_SPARKFUN-DISCRETESEMI_SOT23-3,"Q1, Q3","P-channel MOSFETs",,,,,,,,,,,,,,,,,,,,TRAN-14388,,,,,20V/4.2A/52m?/1.4W
1,2K,ESP32_WROVER_EAGLE-LTSPICE_R,ESP32_WROVER_EAGLE-LTSPICE_R0402,R2_BAT,"RESISTOR, European symbol",,,,,,,,,,,,,,,,,,,,,,,,,
4,4.7uF,EAGLE-LTSPICE_C,ESP32_WROVER_EAGLE-LTSPICE_C0402,"C1, C1_BAT1, C1_BAT2, C5_USB","CAPACITOR, European symbol",,,,,,,,,,,,,,,,,,,,,,,,,
2,4.7uF,ESP32_WROVER_EAGLE-LTSPICE_CC0402,ESP32_WROVER_EAGLE-LTSPICE_C0402,"C1_BAT, C2_BAT","CAPACITOR, European symbol",,,,,,,,,,,,,,,,,,,,,,,NONE,C,
1,4.7uF/25V,ESP32_WROVER_EAGLE-LTSPICE_CC0402,ESP32_WROVER_EAGLE-LTSPICE_C0402,C4,"CAPACITOR, European symbol",,,,,,,,,,,,,,,,,,,,,,,NONE,C,
2,5k1,ESP32_WROVER_EAGLE-LTSPICE_R,ESP32_WROVER_EAGLE-LTSPICE_R0402,"R2-USB, R2-USB1","RESISTOR, European symbol",,,,,,,,,,,,,,,,,,,,,,,,,
1,744043680IND_4828-WE-TPC_WRE,744043680IND_4828-WE-TPC_WRE,IND_4828-WE-TPC_WRE,L1,,,,,,"Copyright (C) 2024 Ultra Librarian. All rights reserved.",,,,744043680,,"Wurth Electronics",,,,,,,,,,,,,,
1,BD5229G-TR,BD5229G-TR,SOT95P280X125-5N,IC2,"Voltage Detector with Adjustable Delay Time: CMOS processes are utilized to develop high precision, low current consumption CMOS reset ICs that allow arbitrary setting of the delay time. The extensive lineup includes both Nch Open Drain and CMOS output types in a wide range of detection voltages (from 2.3V to 6.0V, in 0.1V steps), enabling selection of the ideal solution based on customer requirements. In addition, the entire series is of course both lead-free and RoHS-compliant.",,,,,,"Voltage Detector with Adjustable Delay Time: CMOS processes are utilized to develop high precision"," low current consumption CMOS reset ICs that allow arbitrary setting of the delay time. The extensive lineup includes both Nch Open Drain and CMOS output types in a wide range of detection voltages (from 2.3V to 6.0V"," in 0.1V steps)"," enabling selection of the ideal solution based on customer requirements. In addition"," the entire series is of course both lead-free and RoHS-compliant.",1.25mm,"ROHM Semiconductor",BD5229G-TR,,,755-BD5229G-TR,https://www.mouser.co.uk/ProductDetail/ROHM-Semiconductor/BD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,,,,,,,,
3,BUTTON_CUSYOMV11,BUTTON_CUSYOMV11,MYBUTTON,"BOOT_BUTTON, CHANGE_BUTTON, RESET_BUTTON",,,,,,,,,,,,,,,,,,,,,,,,,,
1,CPH3225A,CPH3225A,CAPCP3225X100N,C10_SUPERCAP,"Cap 0.011F 3.3V 1210 Flat Check availability",,,"Not in stock",https://www.snapeda.com/parts/CPH3225A/Seiko+Instruments/vie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,," 11 mF (EDLC) Supercapacitor 3.3 V 1210 (3225 Metric) - - ",,,,"Seiko Instruments",,,,,,CPH3225A,"1210 Seiko",,None,,"https://www.snapeda.com/api/url_track_click_mouser/?unipart_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 Instruments&part_name=CPH3225A&search_term=None",https://www.snapeda.com/parts/CPH3225A/Seiko+Instruments/vie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,,,
1,DS3231SN#,DS3231SN#,SOIC127P1032X265-16N,U4,"Real Time Clock Serial 16-Pin SOIC W T/R     Check availability",,,"In Stock",https://www.snapeda.com/parts/DS3231SN%23/Analog+Devices/vie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,," Extremely Accurate I2C-Integrated RTC/TCXO/Crystal ",,,,"Analog Devices",,,,,,DS3231SN#,"SOIC-16 Maxim",,None,,"https://www.snapeda.com/api/url_track_click_mouser/?unipart_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 Devices&part_name=DS3231SN#&search_term=None",https://www.snapeda.com/parts/DS3231SN%23/Analog+Devices/vie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,,,
1,ESP32-C6-WROOM-1-N8,ESP32-C6-WROOM-1-N8,XCVR_ESP32-C6-WROOM-1-N8,U2,"Check availability",,,"In Stock",https://www.snapeda.com/parts/ESP32-C6-WROOM-1-N8/Espressif+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,," Multiprotocol Modules ESP32-C6 module"," Wi-Fi 6 in 2.4 GHz band"," Bluetooth 5"," Zigbee 3.0 and Thread. ESP34-WROOM Compatible - ENGINEERING SAMPLE ",,,,"Espressif Systems",,,,,,ESP32-C6-WROOM-1-N8,None,,None,,,https://www.snapeda.com/parts/ESP32-C6-WROOM-1-N8/Espressif+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
1,ESP32C6_VARISTORCN1812,ESP32C6_VARISTORCN1812,ESP32C6_VARISTOR_CT/CN1812,PFMF.050.1,VARISTOR,,,,,,,,,,,,,,,,,,0,,,,,,,
2,ESP32_WROVER_AVX---SD0805S020S1R0_AVX_SD0805S020S1R0_0_0,ESP32_WROVER_AVX---SD0805S020S1R0_AVX_SD0805S020S1R0_0_0,ESP32_WROVER_AVX---SD0805S020S1R0_AVX_SD0805S020S1R0_0,"D2, D7","Schottky Barrier Rectifier Diode",,,,,,,,,,,,,,,,,,,,,,,,,
1,ESP32_WROVER_BME680_BME680,ESP32_WROVER_BME680_BME680,ESP32_WROVER_BME680_PSON80P300X300X100-8N,U1,"Integrated Environmental Unit",,,Unavailable,,," Integrated Environmental Unit ",,,,"Bosch Sensortec",,,,,,BME680,"LGA-8 Bosch Tools",,None,,,,,,
1,ESP32_WROVER_SPARKFUN-IC-POWER_MCP73831,ESP32_WROVER_SPARKFUN-IC-POWER_MCP73831,ESP32_WROVER_SPARKFUN-IC-POWER_SOT23-5,U6,"MCP73831T Li-Ion, Li-Pol Controller",,,,,,,,,,,,,,,,,,,,IC-09995,,,,,
1,FH34SRJ-24S-0.5SH_99_,FH34SRJ-24S-0.5SH_99_,FH34SRJ24S05SH99,J4," (0.50mm) Surface Mount, Right Angle",,,,,,"24 Position FFC"," FPC Connector Contacts"," (0.50mm) Surface Mount"," Right Angle",1.1mm,Hirose,FH34SRJ-24S-0.5SH(99),,,798-FH34SRJ24S05SH99,https://www.mouser.co.uk/ProductDetail/Hirose-Connector/FH34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,,,,,,,,,
1,MAX17048G+T10,MAX17048G+T10,SON50P200X200X80-9N,U3,"Check availability",,,"In Stock",https://www.snapeda.com/parts/MAX17048G+T10/Analog+Devices/v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,," 3µA 1-Cell/2-Cell Fuel Gauge with ModelGauge ",,,,"Analog Devices",,,,,,MAX17048G+T10,"TDFN-8 Maxim",,None,,"https://www.snapeda.com/api/url_track_click_mouser/?unipart_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 Devices&part_name=MAX17048G+T10&search_term=None",https://www.snapeda.com/parts/MAX17048G+T10/Analog+Devices/v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,,,
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
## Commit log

2025-04-06 Create LICENSE
2025-04-06 Create Hardware

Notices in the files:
parts and their libraries:
COPYRIGHT: Copyright (C) 2024 Ultra Librarian. All rights reserved.
